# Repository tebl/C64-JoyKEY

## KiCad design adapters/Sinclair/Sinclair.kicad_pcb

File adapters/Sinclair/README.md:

# JoyKEY (ZX Spectrum +2/+3)
Back in the days when the ZX Spectrum was still all the rage in Europe, but mostly Britain - the Atari joysticks were available from most computer stores. Given that the ZX Spectrum originally lacked a dedicated joystick port, Kempston released an interface that allowed gamers to use an Atari-style joystick with their system. Sinclair, after being bought up by Amstrad added joystick ports to their newly updated machines, but in an attempt to corner the market on the sale of joysticks they changed the pinouts - allowing only the Sinclair SJS to function as expected.

A lengthy story that mostly just explains why an adapter is needed, in the case of the *C64 JoyKEY* this an adapter that let's you connect directly to the mentioned systems (ZX Spectrum +2/+3). This is not needed if the joystick port you are using is on one of the common DivIDE/DivMMC or on a standalone Kempston compatible device, as those are already Atari-compatible interfaces. When soldering together the adapter, you will have the option to add a male DB9 connector as well, allowing you to use it as an adapter with common Atari-style joysticks as well.

The completed adapter can be seen below, this also includes the expected position that should be set on the *C64 JoyKEY* device itself. Note that the Sinclair Interface 2 standard does not officially have a power pin, so the active parts of the *C64 JoyKEY* will not be powered up by the system.

# BOM
The parts listed are the ones I've used when building a Sinclair adapter for use with the *C64 JoyKEY*, part listed in parenthesis are considered optional (meaning you could build a more limited or alternative version of it). Note that depending on the joysticks you want to use with the adapter, you may only need one of the input headers (either IDC or male DB9) - though both would most likely be preferred, as that way you'll have the option later on. 

| Reference     | Item                                      | Count | Order   |
| ------------- | ----------------------------------------- | ----- | ------- |
| PCB           | Fabricate using Gerber files              |     1 | [PCBway](https://www.pcbway.com/project/shareproject/C64_JoyKEY__Sinclair_adapter_.html)
| J1 *          | 2x5 pin straight header pins or 2x5 IDC   |     1 |
| J2 **         | DE-9 Female straight connector            |     1 |
| J3            | DE-9 Male straight connector              |    (1)|

*) Breakable dual row pin headers can be used here, but I find it is nicer to use a 2x5 pin connector here instead. The cable needed is a 2x5 pin IDC cable (usually listed as *AVR* or *JTAG* cable) with sufficient length.

**) These are the blue kind with straight pins, it will include a few metal bits on it - remove those and you'll be left with the mostly blue part needed. Bend the pins slightly and match up with PCB, solder before it has a chance to fall off.

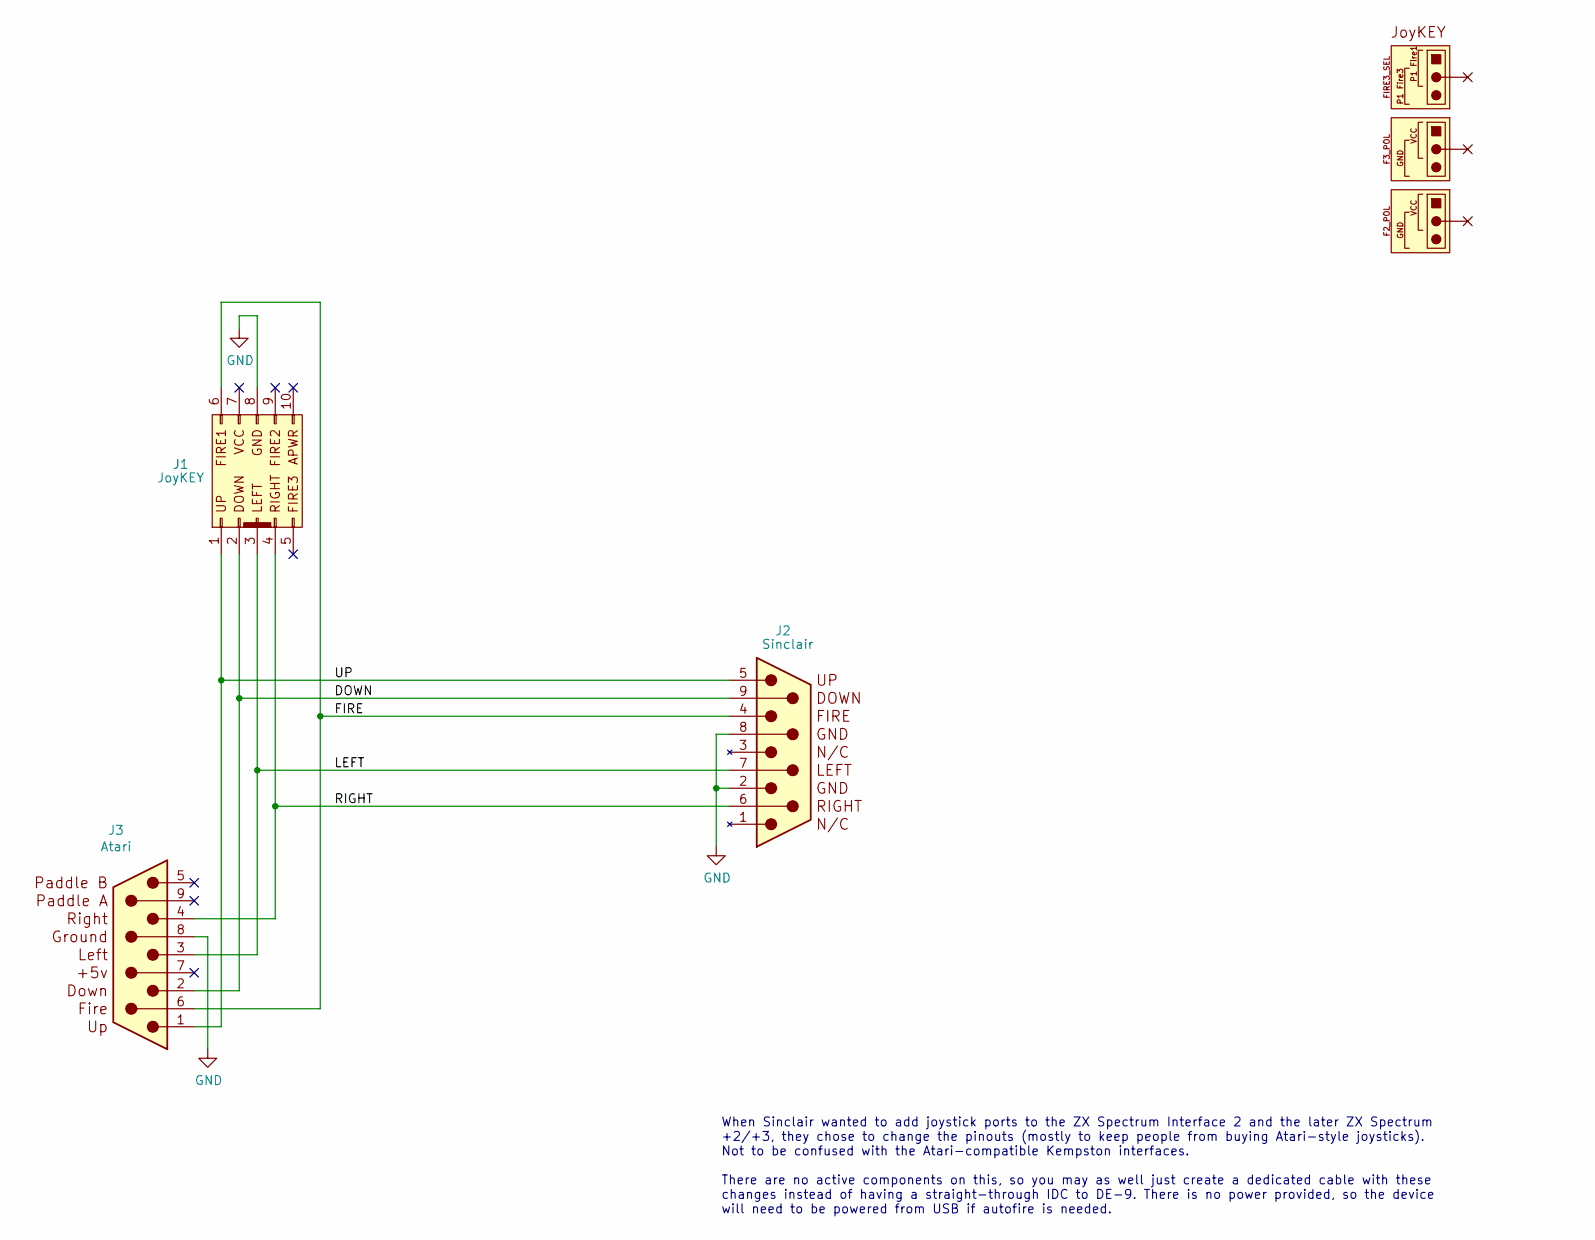
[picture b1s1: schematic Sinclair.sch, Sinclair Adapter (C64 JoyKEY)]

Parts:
J1: JoyKEY; IDC_Joystick
J2: Sinclair; DSUB-9_Female_Edge
J3: Atari; DSUB-9_Male_Edge

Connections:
/DOWN: J1.2, J2.9, J3.2
/FIRE: J1.6, J2.4, J3.6
/LEFT: J1.3, J2.7, J3.3
/RIGHT: J1.4, J2.6, J3.4
/UP: J1.1, J2.5, J3.1
GND: J1.8, J2.2 (GND), J2.8, J3.8 (GND)

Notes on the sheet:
When Sinclair wanted to add joystick ports to the ZX Spectrum Interface 2 and the later ZX Spectrum +2/+3, they chose to change the pinouts (mostly to keep people from buying Atari-style joysticks). Not to be confused with the Atari-compatible Kempston interfaces. There are no active components on 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

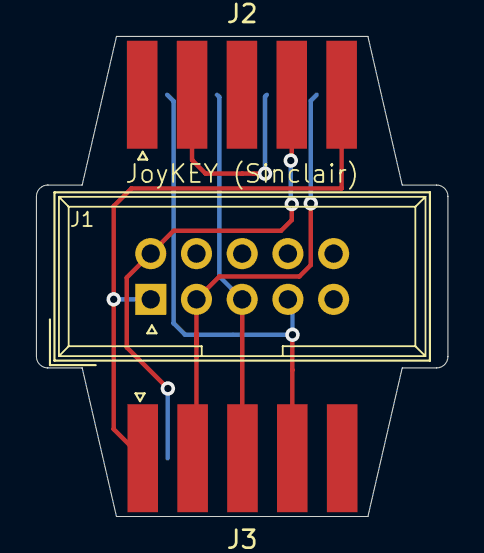
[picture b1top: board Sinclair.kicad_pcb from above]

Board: 2 copper layers, 22.9 x 26.7 mm, 3 parts (0 on the bottom side), 6 nets.
